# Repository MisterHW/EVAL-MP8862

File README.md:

# EVAL-MP8862: I²C-controlled 1 .. 20.47 V / 2 A buck-boost module

EVAL-MP8862 is a compact and self-contained DCDC module for 2.8 .. 22 V in to 1 .. 20.47 V output conversion. It is designed to leverage the features provided by [MP8862GQ-0000](https://www.monolithicpower.com/en/mp8862.html) to provide digital control over the output voltage (10 mV steps) and current limit (50 mA steps or depending on resistor programming).

In its compact 13x25 mm² form factor with 2.54 mm (0.1") pitch pin header, EVAL-MP8862 can be used for evaluation on the breadboard as well as in application circuits. 

The project is created using a nightly build of [KiCad](https://kicad-pcb.org/), and the board files should be supported by KiCad v6 and higher.

**Features**

- 1 .. 20.47 V / 2 A output with optional line drop compensation
- synchronous 4 switch topology with constant on-time / off-time control (buck-/boost-mode)
- I²C interface to adjust voltage in 10 mV steps / current limit in 50 mA steps
- 4 resistor-programmed I²C addresses for bus control of multiple converter modules
- digital CC/CV mode readout
- digital output enable / disable 
- on-board ceramic input and output capacitors
- reduced radiated EMI design with magnetically and electrically shielded power inductor
- 1x05 pin header option for I²C and power 
- 2x05 pin header for full feature set (adds EN enable/!powerdown and ALT alert output)
- factory programming of the default behavior set on EN rising edge

**Caveat**

EVAL-MP8862 can immediately be used for applications that require >= 5.0 V output. A configuration sequence is described below to use the board for lower voltages while respecting maximum output voltage limits. See *One-Time Programmable* below for more details.

## Schematic

## Control Interface

Communication via I²C is described in the [MP8862 datasheet](https://www.monolithicpower.com/en/documentview/productdocument/index/version/2/document_type/Datasheet/lang/en/sku/MP8862/document_id/3999/) ([cached version](doc/MP8862.pdf)).

I²C device addresses can be resistor-programmed with generous tolerance.

I²C communication follows a common [I²C frame structure](img/MP8862_I2C_transfers.PNG) with single and multi-register write, and (officially) single-register read operations. See more below.

The 11 bit voltage setpoint and 7 bit current limit values are configured via VOUT\_H:VOUT\_L and IOUT\_LIM registers. 

Default values can only be set at the factory. The defaults for the marketed -0000 variant are given below. Note in particular that "Output Voltage Discharge Mode" is "Enabled", which ensures a > 50 ms sustain time after EN is pulled low, during which powerdown is not entered and the register contents can be read and written.

### I2C multi-byte reads

"page 23" (no figure number or caption given) shows a single-byte read operation. Since NACK is issued by the bus master, one could test how the device responds to ACK and continued reading of the form:

    S
    deviceAddress << 1 | 0 : ACK : REG_ADDR_K : ACK
    Sr
    deviceAddress << 1 | 1 : ACK : BYTE K [: ACK : BYTE K+1 [ : ... ]] : NACK
    P

Indeed, it turns out that  reading multiple bytes in series is legitimate. The PulseView capture + decoding shows four bytes read, starting at address 0x00:

How far can this be taken? Reading 256 or more bytes:

Several observations can be made: 
1. Reading past ranges of documented registers is allowed.
2. An arbitrary number of bytes can be read.
3. There are non-zero registers outside the documented range of registers.
4. The register counter does not seem to wrap around, even when reading 128 or more bytes.

Here are the register contents after power-up into normal operation with Enable pulled high:

The documented registers are shown on gray background. Some registers which have an actual purpose may read as zero and cannot be recognized as such, and may be read-only, so write-readback tests may fail to expose them.

Testing another chip, the 0x40..0x4F block seems to be identical and probably contains OTP defaults for the registers. The 0x50..0x5F block however contains differing values:

	0x50 : 02 02 C1 00 00 ..
 
One possible explanation is that we are looking at the MP8862 internal calibration coefficients here. MPS determines these in-house for each chip. There is reason to believe that the OTP memory is not divided up into banks for factory calibration and power-up defaults, giving rise to the inconvenience that customers cannot set power-up defaults during their own manufacturing process.

When reading 255 or more bytes, [something bad happens](img/read_0x00_0xFF_uart_starts_out_of_order_STM32F7_potential_problem.PNG) at the end (out-of-order execution of a subsequent UART transmission, NACK and STOP are missing) but probably the STM32F7 I2C master used for testing is to blame in this case.

**To conclude this side quest**, reading multiple consecutive register addresses is proven to work, and (some) defaults seem to be readable. The addresses are not guaranteed and may change with later revisions, but Device ID and IC Revision should make this traceable. The read sequence format is described above, following a regular memory read pattern.

## Power-Up Sequence

EVAL-MP8862-1B has a solder jumper JP1 that ships in an open configuration. The device then defaults to 2 Meg pulldown and stays in powerdown. (The PCB assembly should not be operated in conditions with condensing humidity and surface contamination.)

Regular operation foresees that EN is either pulled up or actively driven by a microcontroller or the output of a digital isolator.

The following section describes a workaround that should allow full control over the module output voltage while using the commercially available MP8862GQ-0000 chip variant.

Hypothesis:

- EN rising edge enables the internal 3.65 V LDO
- internal LDO charges the external 1 µF capacitor within 50-100 µs
- the internal LDO has an internal powergood signal (let's call it LDO.PG)
- LDO.PG enables the I²C peripheral
- LDO.PG enables soft-start charging and power output
- soft-start is sufficiently slow to permit several I²C bytes at < 3400 kHz before the output voltage rises above 1.0V
- Once the device ACKs after a start condition and device address match, EN can be turned off again
- after disabling EN again, the chip stays active for at least 50 ms during which CTL1.EN can be cleared
- device can be safely shut down when a timeout is encountered

The sequence is visualized in the chart below. See the datasheet for statements that support some of the points.

We'd need to decap and investigate one of those chips to see how they're put together, but in the discussion with an MPS FAE we concluded that assuming the I²C peripheral is deterministic in its ACK behavior, this routine should work and unlock the full usability of the MP8862.

I personally remain hopeful that Monolithic Power Systems consider providing another variant that defaults to CTL1.EN = 0 to enable reliable I²C-based control in a stock product, making this workaround obsolete. 

### Update: Experimental Proof

The diagram below shows an MP8862Q-0000 connected to pin 1 of a PCA9536 GPIO expander (address 0x41). Writing to its OUTPUT0 register + STOP causes a 0->1 transition of the MP8862 EN input. Repeated attempts to write CTL1 with an appropriate value (EN = 0) are ultimately effective at disabling the output. This concludes the time-critial part, after which VOUTL, VOUTH and finally GO can be written to update the output voltage setpoint. STATUS is then polled to check for its PG == 1.

The number of attempts is limited to 4 at an I2C clock speed of 400 kHz, allowing just enough time to send another GPIO expander update which would set  the EN input to 0 again within < 200 µs. Using PIO or a faster GPIO expander, 13 (48) attempts are possible at 1 MHz (3.4 MHz).

To ensure voltage excursions are indeed controlled as the converter starts up, the LDO and output voltages can be captured along with the enable pin state. CTL2 defaults to SS = 0b11, or 900 µs ramp time for 0 to 5 V. A 200 µs delay between hardware EN rising edge and CTL1 write STOP can be split up in ~50 µs for LDO.PG delay, and 150 µs into the 900 µs ramp time. This translates into a peak of about 5.0 V * 150 / 900 = 0.83(3) V.

#### Alternative Timing

If this initial transient of < 1 V cannot be tolerated, another start-up sequence can be implemented which creates hardware EN pulses starting at 50 µs and getting longer each time by 10 µs. Adequate discharge time for the LDO bypass capacitor needs to be provided between retries. Immediately disabling hardware EN first allows ~50 ms timeout to configure the device (disable soft EN, set new VOUT) and to re-enable hardware EN.

## "One-Time Programmable"

EVAL-MP8862 is built around the MP8862GQ-0000. The default configuration (0000) of this chip is such that when enabling, the output rises to +5.0 V. The output can be disabled and the voltage setpoint can be configured by setting the appropriate register values. When pulling the EN pin low, MP8862 enters powerdown. When the chip is re-enabled, default register settings are restored, and with them "output ON" and "5.0 V". 

A general purpose digitally controlled variant that defaults to "output disabled on power-up" can be procured upon request only. The FAEs I contacted thankfully responded quickly and were able to provide some insights. The biggest catch is that the term "one-time programmable" used in the datasheet actually is a misnomer: configuration bits are written into OTP memory at the factory, along with timming bits. This ties the behavior configuration to the factory calibration and does not allow the designer to set up the chip via I²C during PCB production. Unfortunately I only realized this when it was too late to scrap the design, as I had assumed that the programming sequence can be obtained by contacting MPS, and then one would be good to go.

In terms of prototyping and small-scale production however, use of a MP8862 variant that has its output disabled on power-up remains hamstringed by limitations introduced by "customization" (RFQ for 100 pc. was irrelevant, so assuming 1-3k MOQ and 6-10 week factory lead time).

It would be greatly appreciated if MPS provided a default-output-off version for purely I²C-based control through distributors like Mouser, but this requires some momentum and popularity to even be economically relevant.

## Revision History

- Revision 1B: 0.4 mm via-in-pad construction changed to 0.3 mm via-in-pad connections, solder jumper JP1 added to detach EN pull-up (fallback to internal 2 Meg pull-down so the DCDC converter stays in powerdown until enabled explicitly via EN high.
- Revision 1A: 11 PCBs assembled with 4.7 µH, 6.8 µH inductors and different numbers of input and output capacitors for noise and stability testing. 

---

**Corrections and Improvements**

Feedback is always welcome.

**Legal Disclaimer**

Excerpts of technical documentation published by the manufacturer (MPS) are reproduced here for the purposes of accurate representation of device properties and technical discussion.

PCB design license: [Creative Commons - Attribution - ShareAlike 3.0](http://creativecommons.org/licenses/by-sa/3.0/)

All files are provided as-is. Physical realization of any circuit requires design review and appropriate selection of components. No responsibilities for damage or harm caused by use of material presented herein will be accepted.

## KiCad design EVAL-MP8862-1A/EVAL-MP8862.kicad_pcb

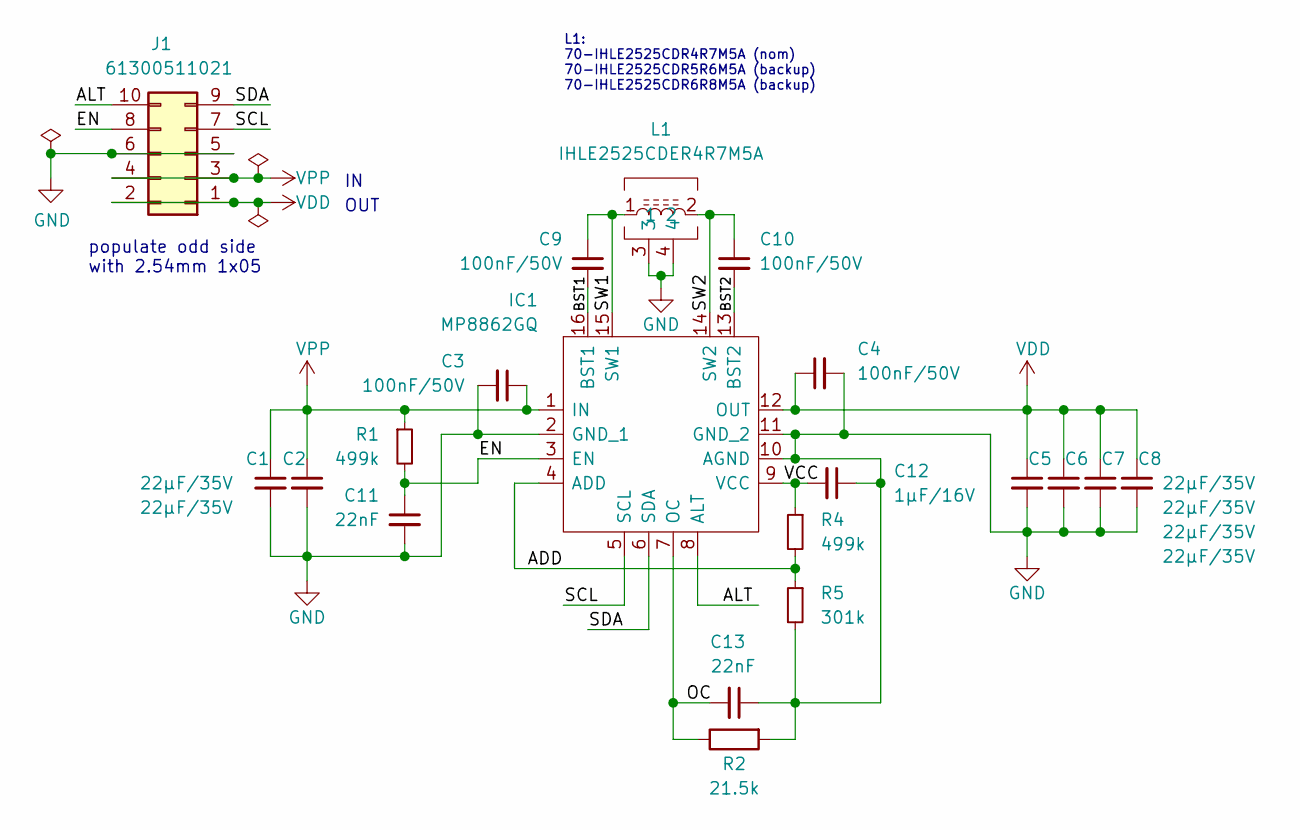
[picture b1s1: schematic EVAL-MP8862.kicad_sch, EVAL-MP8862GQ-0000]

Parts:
C1, C2, C5, C6, C7, C8: 22µF/35V; C_1210_3225Metric; Mouser Part Number 963-GMK325BJ226MM-P
C3, C4, C9, C10: 100nF/50V; C_0603_1608Metric; Mouser Part Number 80-C0603C104K5REC
C11, C13: 22nF; C_0603_1608Metric; Mouser Part Number 80-C0603C223K5REC
C12: 1µF/16V; C_0603_1608Metric; Mouser Part Number 963-TMK107B7105KA-T
IC1: MP8862GQ; Manufacturer_Part_Number MP8862GQ-0000-Z; Mouser Part Number 946-MP8862GQ-0000-Z
J1: 61300511021; PinHeader_2x05_P2.54mm_Horizontal; Mouser Part Number 710-61300511021
L1: IHLE2525CDER4R7M5A; IHLE2525CD; Manufacturer_Part_Number IHLE2525CDER4R7M5A; Mouser Part Number 70-IHLE2525CDR4R7M5A
R1, R4: 499k; R_0603_1608Metric; Mouser Part Number 652-CR0603FX-4993ELF
R2: 21.5k; R_0603_1608Metric; Mouser Part Number 652-CR0603FX-2152ELF
R5: 301k; R_0603_1608Metric; Mouser Part Number 652-CR0603FX-3013ELF

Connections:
/ADD: IC1.4 (ADD), R4.2, R5.1
/ALT: IC1.8 (ALT), J1.10
/BST1: C9.2, IC1.16 (BST1)
/BST2: C10.2, IC1.13 (BST2)
/EN: C11.1, IC1.3 (EN), J1.8, R1.2
/OC: C13.2, IC1.7 (OC), R2.1
/SCL: IC1.5 (SCL), J1.7
/SDA: IC1.6 (SDA), J1.9
/SW1: C9.1, IC1.15 (SW1), L1.1
/SW2: C10.1, IC1.14 (SW2), L1.2
/VCC: C12.2, IC1.9 (VCC), R4.1
GND: C1.2, C2.2, C3.2, C4.2, C5.2, C6.2, C7.2, C8.2, C11.2, C12.1, C13.1, IC1.2 (GND_1), IC1.10 (AGND), IC1.11 (GND_2), J1.5, J1.6, L1.3, L1.4, R2.2, R5.2
VDD: C4.1, C5.1, C6.1, C7.1, C8.1, IC1.12 (OUT), J1.1, J1.2
VPP: C1.1, C2.1, C3.1, IC1.1 (IN), J1.3, J1.4, R1.1

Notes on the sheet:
populate odd side with 2.54mm 1x05
OUT
L1: 70-IHLE2525CDR4R7M5A (nom) 70-IHLE2525CDR5R6M5A (backup) 70-IHLE2525CDR6R8M5A (backup)

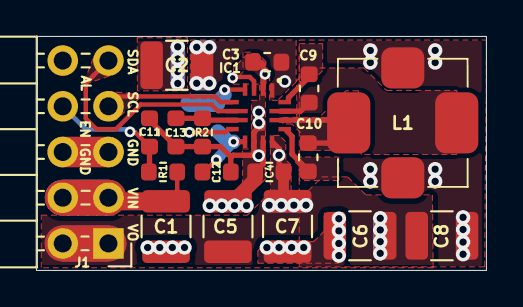
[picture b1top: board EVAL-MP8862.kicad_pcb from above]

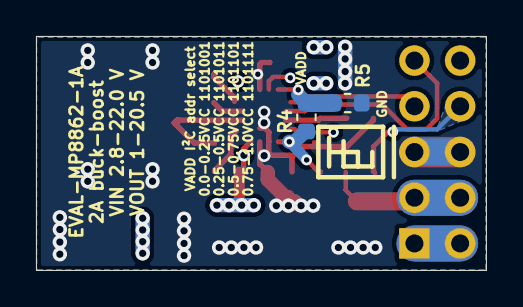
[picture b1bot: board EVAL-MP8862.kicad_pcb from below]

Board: 4 copper layers, 25.0 x 13.0 mm, 20 parts (2 on the bottom side), 14 nets.

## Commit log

2020-10-24 initial commit: restored revision 1A, modified revision 1B.
2020-10-24 add readme with documentation
2020-10-24 update board stack-up info
2020-10-25 recalculated zone fills after a zone fill issue got resolved: smoother zone contours.
2021-08-16 add multi-byte read documentation
2021-08-16 update readme imd paths
2021-08-18 proof of power-up sequence: I2C timing
    changes get applied when STOP condition occurs or when GO is written.
2021-08-18 update I2C capture comments
2021-08-19 improve diagram
2021-08-20 add PCB assembly pictures for documentation
2021-12-25 provide c++ library
    Device library for STM32F7 using HAL I²C functions.
